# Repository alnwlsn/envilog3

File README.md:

# envilog3
2022 version of my enviromental logger board - original version documented on [Hackaday.io](https://hackaday.io/project/160740-low-power-environment-monitor-logger) or [my website](https://alnwlsn.com/projectrepository/index.php/Electronic_Time_Capsule).

This is a little board that I packed with batteries, some sensors, a Flash chip, and an RTC. When the RTC wakes up the board on some interval (programmable; minutes to an hour), it reads the sensors and stores the data in the Flash chip. The rest of the time, the board is in a low power sleep state, drawing <10uA. With 4xAA cells of power, the whole thing should run for several years.

I added a bunch of sensor footprints to this version because I had space and wasn't sure which ones I'd be able to get in the 2022 chip shortage. But, the firmware provided is for this configuration:
* BME280 (pressure, temperature, humidity)
* SHT31-DIS (temperature, humidity)
* BH1730FVC (light sensor; visible & IR)
* DS3232M (Real-time clock chip, also contains temperature sensor)
* Battery voltage (using Atmega ADC & voltage divider)
* 16MB of Flash; enough for 512K samples.
  * This is about 1 year of data at a 1 minute interval. Scale as needed - I'm going for 6 minute interval --> 6 years.

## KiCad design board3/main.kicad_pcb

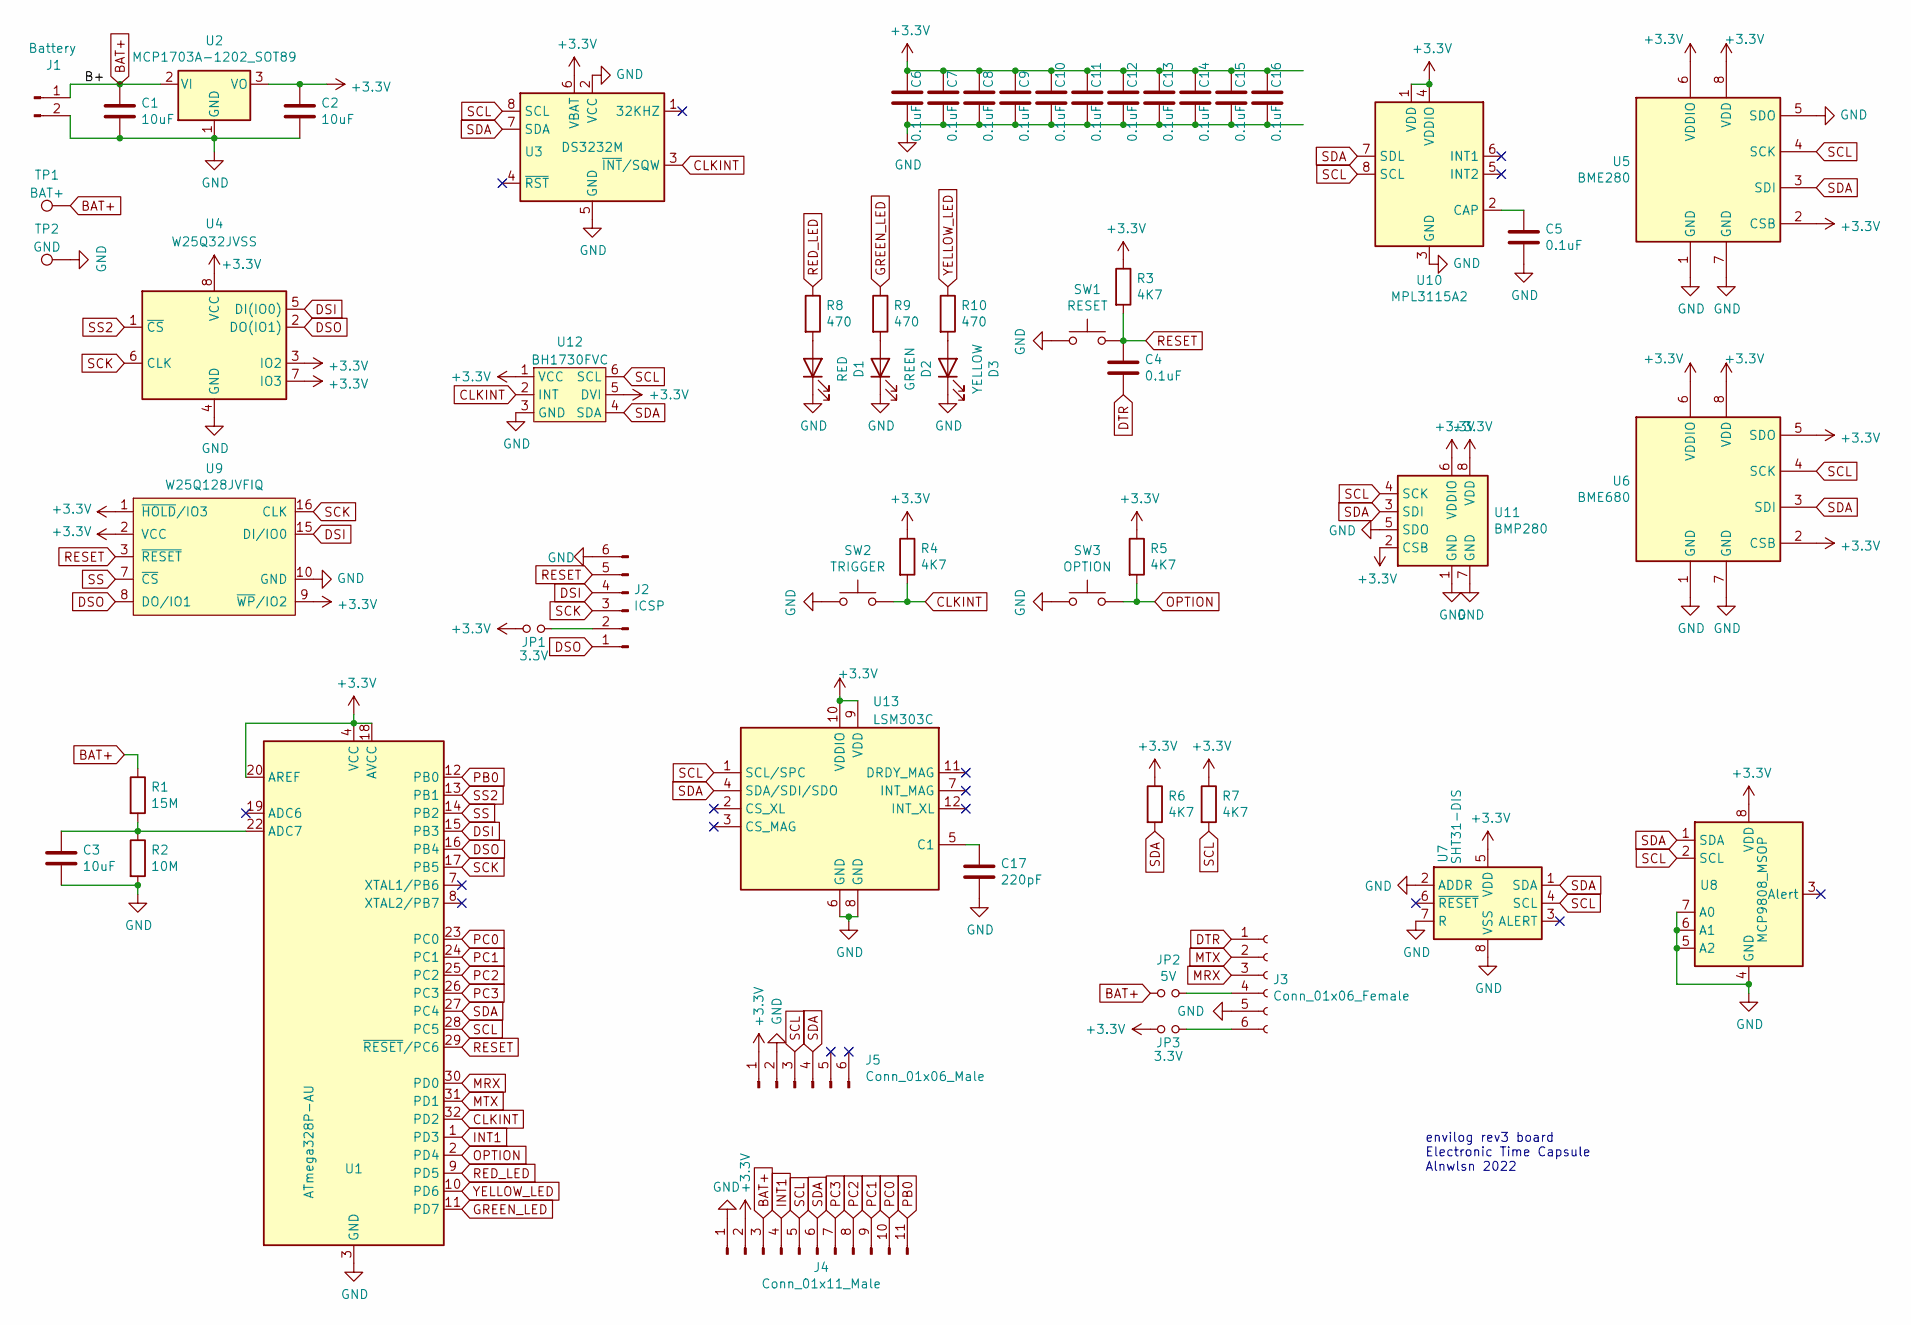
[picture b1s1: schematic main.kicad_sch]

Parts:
C1, C2, C3: 10uF; C_0805_2012Metric
C4, C5, C6, C7, C8, C9, C10, C11, C12, C13, C14, C15, C16: 0.1uF; C_0805_2012Metric
C17: 220pF; C_0805_2012Metric
D1: RED; LED_0805_2012Metric
D2: GREEN; LED_0805_2012Metric
D3: YELLOW; LED_0805_2012Metric
J1: Battery; PinHeader_1x02_P2.54mm_Vertical
J2: ICSP; PinHeader_2x03_P2.54mm_Vertical
J3: Conn_01x06_Female; PinSocket_1x06_P2.54mm_Vertical
J4: Conn_01x11_Male; PinHeader_1x11_P2.54mm_Vertical
J5: Conn_01x06_Male; PinHeader_1x06_P2.54mm_Vertical
JP1, JP3: 3.3V; SolderJumper-2_P1.3mm_Open_RoundedPad1.0x1.5mm
JP2: 5V; SolderJumper-2_P1.3mm_Open_RoundedPad1.0x1.5mm
R1: 15M; R_0805_2012Metric
R2: 10M; R_0805_2012Metric
R3, R4, R5, R6, R7: 4K7; R_0805_2012Metric
R8, R9, R10: 470; R_0805_2012Metric
SW1: RESET; SW_SPST_SKQG_WithStem
SW2: TRIGGER; SW_SPST_SKQG_WithStem
SW3: OPTION; SW_SPST_SKQG_WithStem
TP1: BAT+; 4mm-bslot
TP2: GND; 4mm-bslot
U1: ATmega328P-AU; TQFP-32_7x7mm_P0.8mm
U2: MCP1703A-1202_SOT89; SOT-89-3
U3: DS3232M; SOIC-8_3.9x4.9mm_P1.27mm
U4: W25Q32JVSS; SOIC-8_5.23x5.23mm_P1.27mm
U5: BME280; Bosch_LGA-8_2.5x2.5mm_P0.65mm_ClockwisePinNumbering
U6: BME680; Bosch_LGA-8_3x3mm_P0.8mm_ClockwisePinNumbering
U7: SHT31-DIS; Sensirion_DFN-8-1EP_2.5x2.5mm_P0.5mm_EP1.1x1.7mm
U8: MCP9808_MSOP; MSOP-8_3x3mm_P0.65mm
U9: W25Q128JVFIQ; SOIC-16W_7.5x10.3mm_P1.27mm
U10: MPL3115A2; NXP_LGA-8_3x5mm_P1.25mm_H1.1mm
U11: BMP280; Bosch_LGA-8_2x2.5mm_P0.65mm_ClockwisePinNumbering
U12: BH1730FVC; WSOF-6
U13: LSM303C; LGA-12_2x2mm_P0.5mm

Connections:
+3V3: C2.1, C6.1, C7.1, C8.1, C9.1, C10.1, C11.1, C12.1, C13.1, C14.1, C15.1, C16.1, J4.2, J5.1, JP1.1, JP3.1, R3.1, R4.1, R5.1, R6.1, R7.1, U1.4 (VCC), U1.6 (VCC), U1.18 (AVCC), U1.20 (AREF), U2.3 (VO), U3.6 (VBAT), U4.3 (IO2), U4.7 (IO3), U4.8 (VCC), U5.2 (CSB), U5.6 (VDDIO), U5.8 (VDD), U6.2 (CSB), U6.5 (SDO), U6.6 (VDDIO), U6.8 (VDD), U7.5 (VDD), U8.8 (VDD), U9.1 (~HOLD/IO3), U9.2 (VCC), U9.9 (~WP/IO2), U10.1 (VDD), U10.4 (VDDIO), U11.2 (CSB), U11.6 (VDDIO), U11.8 (VDD), U12.1 (VCC), U12.5 (DVI), U13.9 (VDD), U13.10 (VDDIO)
BAT+: C1.2, J1.1, J4.3, JP2.1, R1.1, TP1.1, U2.2 (VI)
CLKINT: R4.2, SW2.2, U1.32 (PD2), U3.3 (~INT/SQW), U12.2 (INT)
DSI: J2.4, U1.15 (PB3), U4.5 (DI(IO0)), U9.15 (DI/IO0)
DSO: J2.1, U1.16 (PB4), U4.2 (DO(IO1)), U9.8 (DO/IO1)
DTR: C4.2, J3.1
GND: C1.1, C2.2, C3.2, C5.2, C6.2, C7.2, C8.2, C9.2, C10.2, C11.2, C12.2, C13.2, C14.2, C15.2, C16.2, C17.2, D1.1 (K), D2.1 (K), D3.1 (K), J1.2, J2.6, J3.5, J4.1, J5.2, R2.2, SW1.1, SW2.1, SW3.1, TP2.1, U1.3 (GND), U1.5 (GND), U1.21 (GND), U2.1 (GND), U3.2 (VCC), U3.5 (GND), U4.4 (GND), U5.1 (GND), U5.5 (SDO), U5.7 (GND), U6.1 (GND), U6.7 (GND), U7.2 (ADDR), U7.7 (R), U7.8 (VSS), U7.9 (VSS), U8.4 (GND), U8.5 (A2), U8.6 (A1), U8.7 (A0), U9.10 (GND), U10.3 (GND), U11.1 (GND), U11.5 (SDO), U11.7 (GND), U12.3 (GND), U13.6 (GND), U13.8 (GND)
GREEN_LED: R9.1, U1.11 (PD7)
INT1: J4.4, U1.1 (PD3)
MRX: J3.3, U1.30 (PD0)
MTX: J3.2, U1.31 (PD1)
unnamed: C3.1, R1.2, R2.1, U1.22 (ADC7)
unnamed: C5.1, U10.2 (CAP)
unnamed: C17.1, U13.5 (C1)
unnamed: D1.2 (A), R8.2
unnamed: D2.2 (A), R9.2
unnamed: D3.2 (A), R10.2
unnamed: J2.2, JP1.2
unnamed: J3.4, JP2.2
unnamed: J3.6, JP3.2
OPTION: R5.2, SW3.2, U1.2 (PD4)
PB0: J4.11, U1.12 (PB0)
PC0: J4.10, U1.23 (PC0)
PC1: J4.9, U1.24 (PC1)
PC2: J4.8, U1.25 (PC2)
PC3: J4.7, U1.26 (PC3)
RED_LED: R8.1, U1.9 (PD5)
RESET: C4.1, J2.5, R3.2, SW1.2, U1.29 (~RESET/PC6), U9.3 (~RESET)
SCK: J2.3, U1.17 (PB5), U4.6 (CLK), U9.16 (CLK)
SCL: J4.5, J5.3, R7.2, U1.28 (PC5), U3.8 (SCL), U5.4 (SCK), U6.4 (SCK), U7.4 (SCL), U8.2 (SCL), U10.8 (SCL), U11.4 (SCK), U12.6 (SCL), U13.1 (SCL/SPC)
SDA: J4.6, J5.4, R6.2, U1.27 (PC4), U3.7 (SDA), U5.3 (SDI), U6.3 (SDI), U7.1 (SDA), U8.1 (SDA), U10.7 (SDL), U11.3 (SDI), U12.4 (SDA), U13.4 (SDA/SDI/SDO)
SS: U1.14 (PB2), U9.7 (~CS)
SS2: U1.13 (PB1), U4.1 (~CS)
YELLOW_LED: R10.1, U1.10 (PD6)

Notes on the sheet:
envilog rev3 board Electronic Time Capsule Alnwlsn 2022

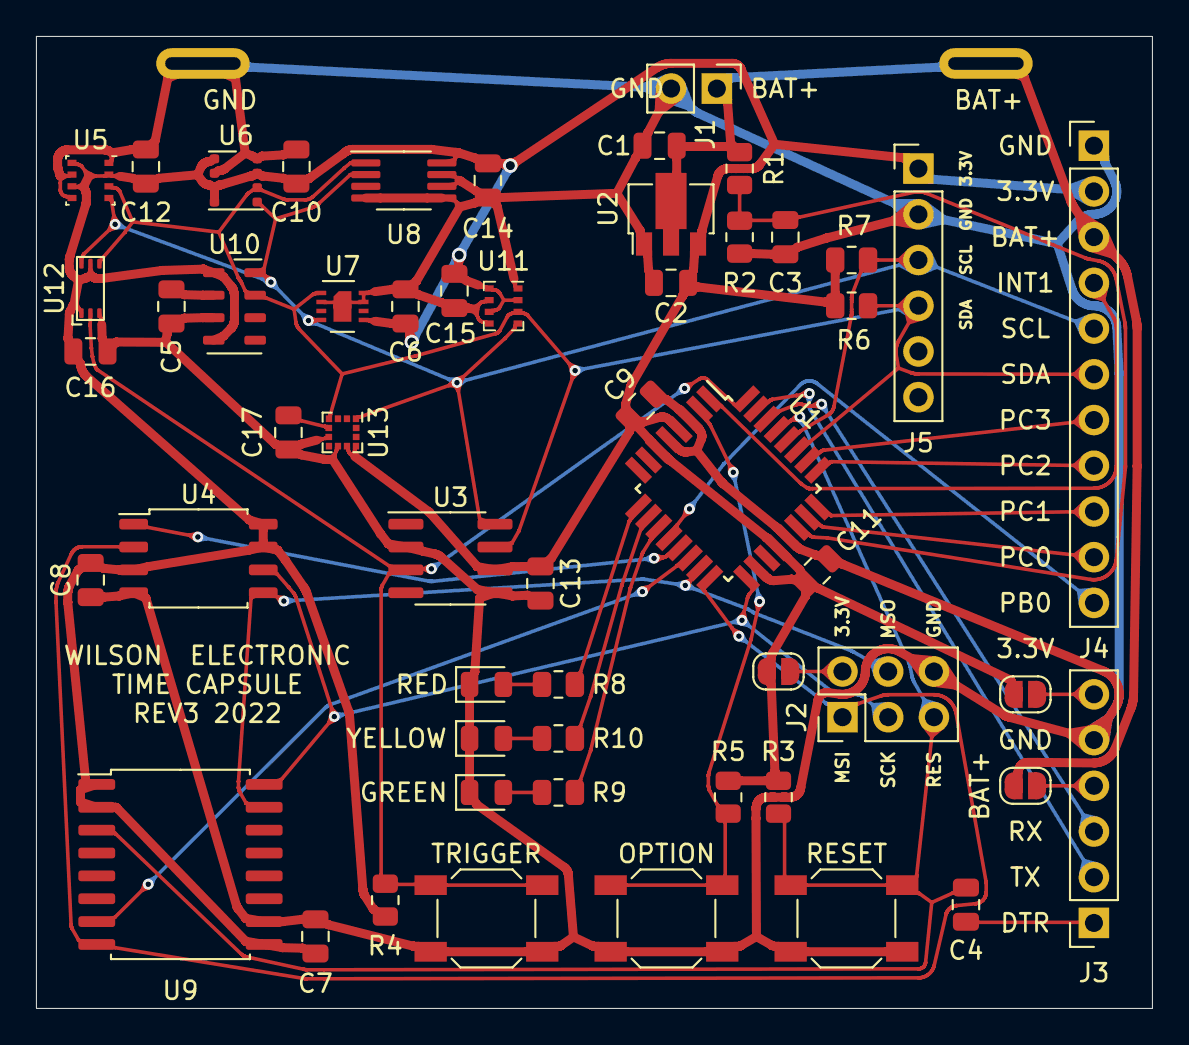
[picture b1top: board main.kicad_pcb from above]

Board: 2 copper layers, 62.0 x 54.0 mm, 56 parts (0 on the bottom side), 34 nets.

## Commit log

2022-04-26 envilog3 - init - board & firmware
2022-12-01 wc xlvi
2022-12-01 reset fix
